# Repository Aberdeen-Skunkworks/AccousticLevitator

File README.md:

# Accoustic Levitator

A device for trapping and manipulating particles in three dimensions as well as the software to simulate these traps.

This Project is split into two distinct sections (1) The control software for the physical array, (2) The acoustic simulation to model the fields produced by this array.

The goal is to have a system that can self-calibrate where the control software can detect and automatically figure out where multiple acoustic arrays are in relation to each other, (Using the -> Aberdeen-Skunkworks/AccousticTracker project) It can then take this positional information and form acoustic traps at desired locations.

The files in the /eagle folder are PCB design files that use the Autodesk PCB design software Eagle which can be found here: https://www.autodesk.com/products/eagle/overview

The files in the /FPGA folder are the setup files that are running on the Field-Programable Gate Arrays that create the ultrasonic signals that are sent to the transducers.

# (1) Control software

# (2) Acoustic simulation

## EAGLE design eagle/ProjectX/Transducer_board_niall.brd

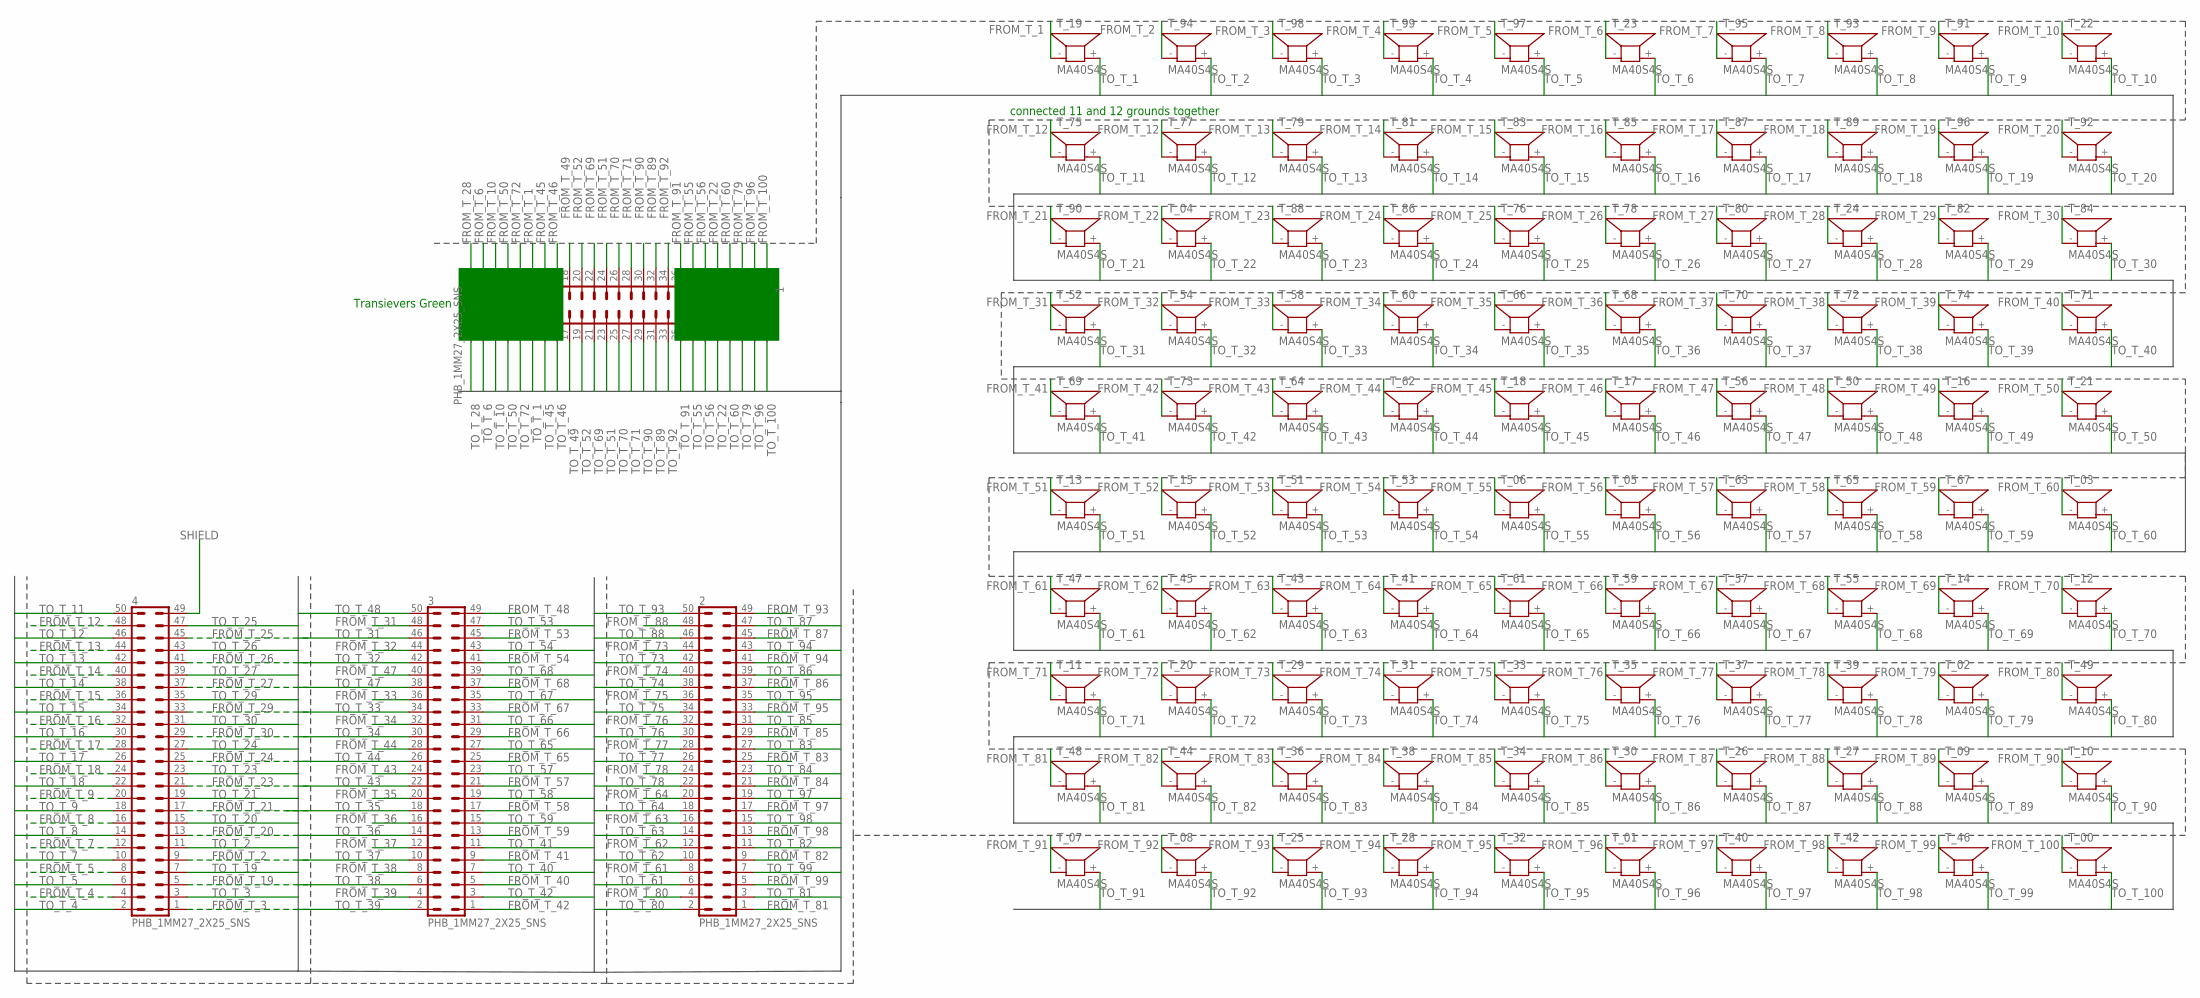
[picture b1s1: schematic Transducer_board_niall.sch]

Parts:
1, 2, 3, 4: PHB_1MM27_2X25_SNS
T_00, T_01, T_02, T_03, T_04, T_05, T_06, T_07, T_08, T_09, T_10, T_11, T_12, T_13, T_14, T_15, T_16, T_17, T_18, T_19, T_20, T_21, T_22, T_23, T_24, T_25, T_26, T_27, T_28, T_29, T_30, T_31, T_32, T_33, T_34, T_35, T_36, T_37, T_38, T_39, T_40, T_41, T_42, T_43, T_44, T_45, T_46, T_47, T_48, T_49, T_50, T_51, T_52, T_53, T_54, T_55, T_56, T_57, T_58, T_59, T_60, T_61, T_62, T_63, T_64, T_65, T_66, T_67, T_68, T_69, T_70, T_71, T_72, T_73, T_74, T_75, T_76, T_77, T_78, T_79, T_80, T_81, T_82, T_83, T_84, T_85, T_86, T_87, T_88, T_89, T_90, T_91, T_92, T_93, T_94, T_95, T_96, T_97, T_98, T_99: MA40S4S; MA40

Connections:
FROM_T_1: 1.12, T_19.- (1)
FROM_T_2: 4.9, T_94.- (1)
FROM_T_3: 4.1, T_98.- (1)
FROM_T_4: 4.4, T_99.- (1)
FROM_T_5: 4.8, T_97.- (1)
FROM_T_6: 1.4, T_23.- (1)
FROM_T_7: 4.12, T_95.- (1)
FROM_T_8: 4.16, T_93.- (1)
FROM_T_9: 4.20, T_91.- (1)
FROM_T_10: 1.6, T_22.- (1)
FROM_T_12: 4.48, T_75.- (1), T_77.- (1)
FROM_T_13: 4.44, T_79.- (1)
FROM_T_14: 4.40, T_81.- (1)
FROM_T_15: 4.36, T_83.- (1)
FROM_T_16: 4.32, T_85.- (1)
FROM_T_17: 4.28, T_87.- (1)
FROM_T_18: 4.24, T_89.- (1)
FROM_T_19: 4.5, T_96.- (1)
FROM_T_20: 4.13, T_92.- (1)
FROM_T_21: 4.17, T_90.- (1)
FROM_T_22: 1.42, T_04.- (1)
FROM_T_23: 4.21, T_88.- (1)
FROM_T_24: 4.25, T_86.- (1)
FROM_T_25: 4.45, T_76.- (1)
FROM_T_26: 4.41, T_78.- (1)
FROM_T_27: 4.37, T_80.- (1)
FROM_T_28: 1.2, T_24.- (1)
FROM_T_29: 4.33, T_82.- (1)
FROM_T_30: 4.29, T_84.- (1)
FROM_T_31: 3.48, T_52.- (1)
FROM_T_32: 3.44, T_54.- (1)
FROM_T_33: 3.36, T_58.- (1)
FROM_T_34: 3.32, T_60.- (1)
FROM_T_35: 3.20, T_66.- (1)
FROM_T_36: 3.16, T_68.- (1)
FROM_T_37: 3.12, T_70.- (1)
FROM_T_38: 3.8, T_72.- (1)
FROM_T_39: 3.4, T_74.- (1)
FROM_T_40: 3.5, T_71.- (1)
FROM_T_41: 3.9, T_69.- (1)
FROM_T_42: 3.1, T_73.- (1)
FROM_T_43: 3.24, T_64.- (1)
FROM_T_44: 3.28, T_62.- (1)
FROM_T_45: 1.14, T_18.- (1)
FROM_T_46: 1.16, T_17.- (1)
FROM_T_47: 3.40, T_56.- (1)
FROM_T_48: 3.49, T_50.- (1)
FROM_T_49: 1.18, T_16.- (1)
FROM_T_50: 1.8, T_21.- (1)
FROM_T_51: 1.24, T_13.- (1)
FROM_T_52: 1.20, T_15.- (1)
FROM_T_53: 3.45, T_51.- (1)
FROM_T_54: 3.41, T_53.- (1)
FROM_T_55: 1.38, T_06.- (1)
FROM_T_56: 1.40, T_05.- (1)
FROM_T_57: 3.21, T_63.- (1)
FROM_T_58: 3.17, T_65.- (1)
FROM_T_59: 3.13, T_67.- (1)
FROM_T_60: 1.44, T_03.- (1)
FROM_T_61: 2.8, T_47.- (1)
FROM_T_62: 2.12, T_45.- (1)
FROM_T_63: 2.16, T_43.- (1)
FROM_T_64: 2.20, T_41.- (1)
FROM_T_65: 3.25, T_61.- (1)
FROM_T_66: 3.29, T_59.- (1)
FROM_T_67: 3.33, T_57.- (1)
FROM_T_68: 3.37, T_55.- (1)
FROM_T_69: 1.22, T_14.- (1)
FROM_T_70: 1.26, T_12.- (1)
FROM_T_71: 1.28, T_11.- (1)
FROM_T_72: 1.10, T_20.- (1)
FROM_T_73: 2.44, T_29.- (1)
FROM_T_74: 2.40, T_31.- (1)
FROM_T_75: 2.36, T_33.- (1)
FROM_T_76: 2.32, T_35.- (1)
FROM_T_77: 2.28, T_37.- (1)
FROM_T_78: 2.24, T_39.- (1)
FROM_T_79: 1.46, T_02.- (1)
FROM_T_80: 2.4, T_49.- (1)
FROM_T_81: 2.1, T_48.- (1)
FROM_T_82: 2.9, T_44.- (1)
FROM_T_83: 2.25, T_36.- (1)
FROM_T_84: 2.21, T_38.- (1)
FROM_T_85: 2.29, T_34.- (1)
FROM_T_86: 2.37, T_30.- (1)
FROM_T_87: 2.45, T_26.- (1)
FROM_T_88: 2.48, T_27.- (1)
FROM_T_89: 1.32, T_09.- (1)
FROM_T_90: 1.30, T_10.- (1)
FROM_T_91: 1.36, T_07.- (1)
FROM_T_92: 1.34, T_08.- (1)
FROM_T_93: 2.49, T_25.- (1)
FROM_T_94: 2.41, T_28.- (1)
FROM_T_95: 2.33, T_32.- (1)
FROM_T_96: 1.48, T_01.- (1)
FROM_T_97: 2.17, T_40.- (1)
FROM_T_98: 2.13, T_42.- (1)
FROM_T_99: 2.5, T_46.- (1)
FROM_T_100: 1.50, T_00.- (1)
SHIELD: 4.49
TO_T_1: 1.11, T_19.+ (2)
TO_T_2: 4.11, T_94.+ (2)
TO_T_3: 4.3, T_98.+ (2)
TO_T_4: 4.2, T_99.+ (2)
TO_T_5: 4.6, T_97.+ (2)
TO_T_6: 1.3, T_23.+ (2)
TO_T_7: 4.10, T_95.+ (2)
TO_T_8: 4.14, T_93.+ (2)
TO_T_9: 4.18, T_91.+ (2)
TO_T_10: 1.5, T_22.+ (2)
TO_T_11: 4.50, T_75.+ (2)
TO_T_12: 4.46, T_77.+ (2)
TO_T_13: 4.42, T_79.+ (2)
TO_T_14: 4.38, T_81.+ (2)
TO_T_15: 4.34, T_83.+ (2)
TO_T_16: 4.30, T_85.+ (2)
TO_T_17: 4.26, T_87.+ (2)
TO_T_18: 4.22, T_89.+ (2)
TO_T_19: 4.7, T_96.+ (2)
TO_T_20: 4.15, T_92.+ (2)
TO_T_21: 4.19, T_90.+ (2)
TO_T_22: 1.41, T_04.+ (2)
TO_T_23: 4.23, T_88.+ (2)
TO_T_24: 4.27, T_86.+ (2)
TO_T_25: 4.47, T_76.+ (2)
TO_T_26: 4.43, T_78.+ (2)
TO_T_27: 4.39, T_80.+ (2)
TO_T_28: 1.1, T_24.+ (2)
TO_T_29: 4.35, T_82.+ (2)
TO_T_30: 4.31, T_84.+ (2)
TO_T_31: 3.46, T_52.+ (2)
TO_T_32: 3.42, T_54.+ (2)
TO_T_33: 3.34, T_58.+ (2)
TO_T_34: 3.30, T_60.+ (2)
TO_T_35: 3.18, T_66.+ (2)
TO_T_36: 3.14, T_68.+ (2)
TO_T_37: 3.10, T_70.+ (2)
TO_T_38: 3.6, T_72.+ (2)
TO_T_39: 3.2, T_74.+ (2)
TO_T_40: 3.7, T_71.+ (2)
TO_T_41: 3.11, T_69.+ (2)
TO_T_42: 3.3, T_73.+ (2)
TO_T_43: 3.22, T_64.+ (2)
TO_T_44: 3.26, T_62.+ (2)
TO_T_45: 1.13, T_18.+ (2)
TO_T_46: 1.15, T_17.+ (2)
TO_T_47: 3.38, T_56.+ (2)
TO_T_48: 3.50, T_50.+ (2)
TO_T_49: 1.17, T_16.+ (2)
TO_T_50: 1.7, T_21.+ (2)
TO_T_51: 1.23, T_13.+ (2)
TO_T_52: 1.19, T_15.+ (2)
TO_T_53: 3.47, T_51.+ (2)
TO_T_54: 3.43, T_53.+ (2)
TO_T_55: 1.37, T_06.+ (2)
TO_T_56: 1.39, T_05.+ (2)
TO_T_57: 3.23, T_63.+ (2)
TO_T_58: 3.19, T_65.+ (2)
TO_T_59: 3.15, T_67.+ (2)
TO_T_60: 1.43, T_03.+ (2)
TO_T_61: 2.6, T_47.+ (2)
TO_T_62: 2.10, T_45.+ (2)
TO_T_63: 2.14, T_43.+ (2)
TO_T_64: 2.18, T_41.+ (2)
TO_T_65: 3.27, T_61.+ (2)
TO_T_66: 3.31, T_59.+ (2)
TO_T_67: 3.35, T_57.+ (2)
TO_T_68: 3.39, T_55.+ (2)
TO_T_69: 1.21, T_14.+ (2)
TO_T_70: 1.25, T_12.+ (2)
TO_T_71: 1.27, T_11.+ (2)
TO_T_72: 1.9, T_20.+ (2)
TO_T_73: 2.42, T_29.+ (2)
TO_T_74: 2.38, T_31.+ (2)
TO_T_75: 2.34, T_33.+ (2)
TO_T_76: 2.30, T_35.+ (2)
TO_T_77: 2.26, T_37.+ (2)
TO_T_78: 2.22, T_39.+ (2)
TO_T_79: 1.45, T_02.+ (2)
TO_T_80: 2.2, T_49.+ (2)
TO_T_81: 2.3, T_48.+ (2)
TO_T_82: 2.11, T_44.+ (2)
TO_T_83: 2.27, T_36.+ (2)
TO_T_84: 2.23, T_38.+ (2)
TO_T_85: 2.31, T_34.+ (2)
TO_T_86: 2.39, T_30.+ (2)
TO_T_87: 2.47, T_26.+ (2)
TO_T_88: 2.46, T_27.+ (2)
TO_T_89: 1.31, T_09.+ (2)
TO_T_90: 1.29, T_10.+ (2)
TO_T_91: 1.35, T_07.+ (2)
TO_T_92: 1.33, T_08.+ (2)
TO_T_93: 2.50, T_25.+ (2)
TO_T_94: 2.43, T_28.+ (2)
TO_T_95: 2.35, T_32.+ (2)
TO_T_96: 1.47, T_01.+ (2)
TO_T_97: 2.19, T_40.+ (2)
TO_T_98: 2.15, T_42.+ (2)
TO_T_99: 2.7, T_46.+ (2)
TO_T_100: 1.49, T_00.+ (2)

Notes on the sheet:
Transievers Green
connected 11 and 12 grounds together

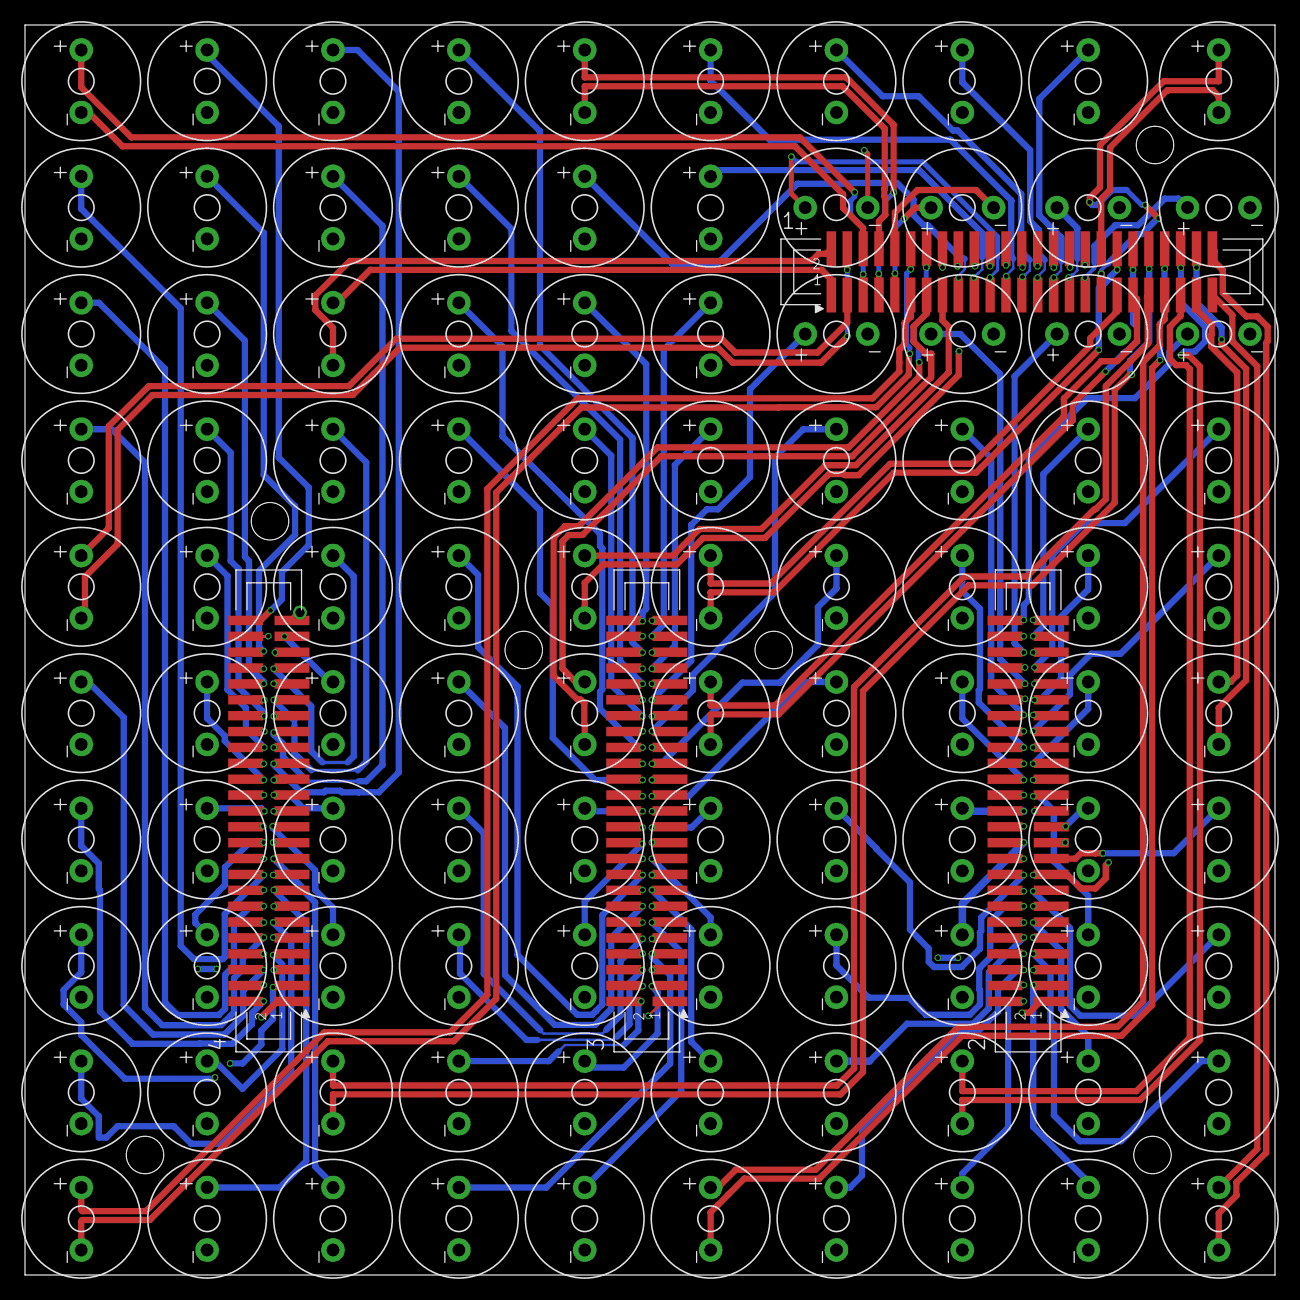
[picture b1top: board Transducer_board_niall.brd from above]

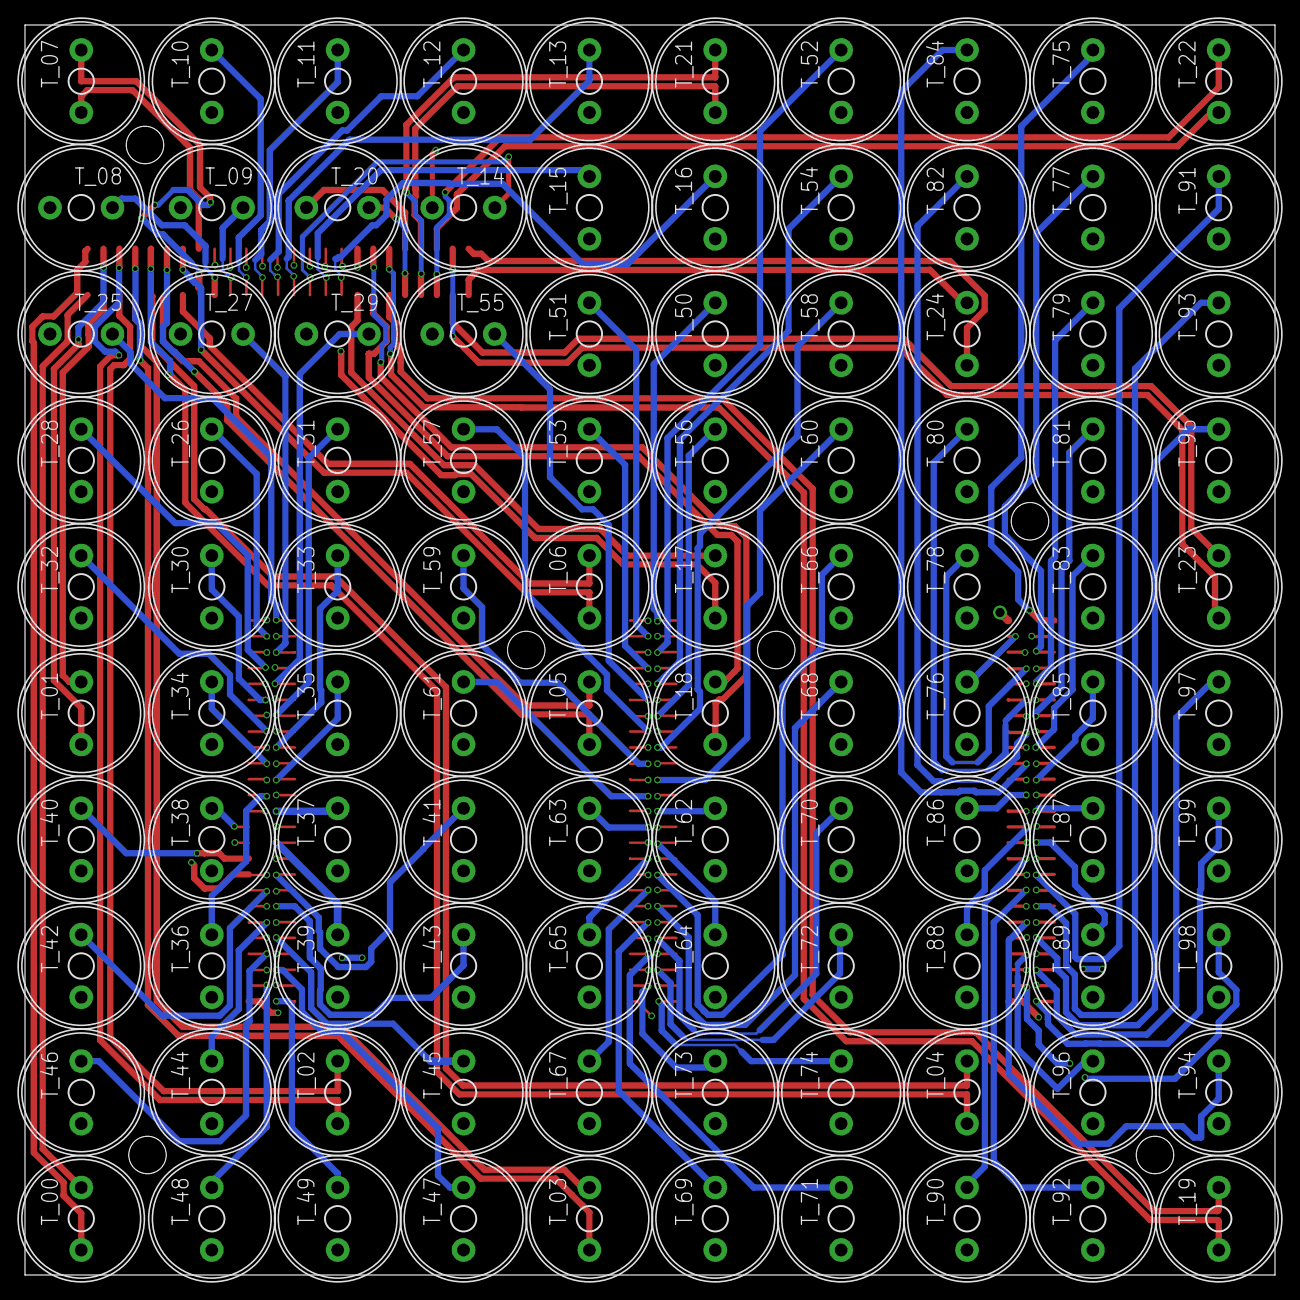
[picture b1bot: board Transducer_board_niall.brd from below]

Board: 4 copper layers, 100.0 x 100.0 mm, 104 parts (100 on the bottom side), 199 nets.

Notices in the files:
parts and their libraries:
SparkFun-Connectors: Licensing: Creative Commons ShareAlike 4.0 International - https://creativecommons.org/licenses/by-sa/4.0
